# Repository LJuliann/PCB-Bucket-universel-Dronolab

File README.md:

# PCB Bucket universel — Dronolab

Conception électronique et routage KiCad du PCB Bucket universel de Dronolab.

## Projet principal

Ouvrir `Bucket_universel_v2.kicad_pro` dans KiCad.

Le dépôt contient le schéma principal, les feuilles hiérarchiques, le circuit imprimé,
les bibliothèques personnalisées et les fichiers de fabrication associés.

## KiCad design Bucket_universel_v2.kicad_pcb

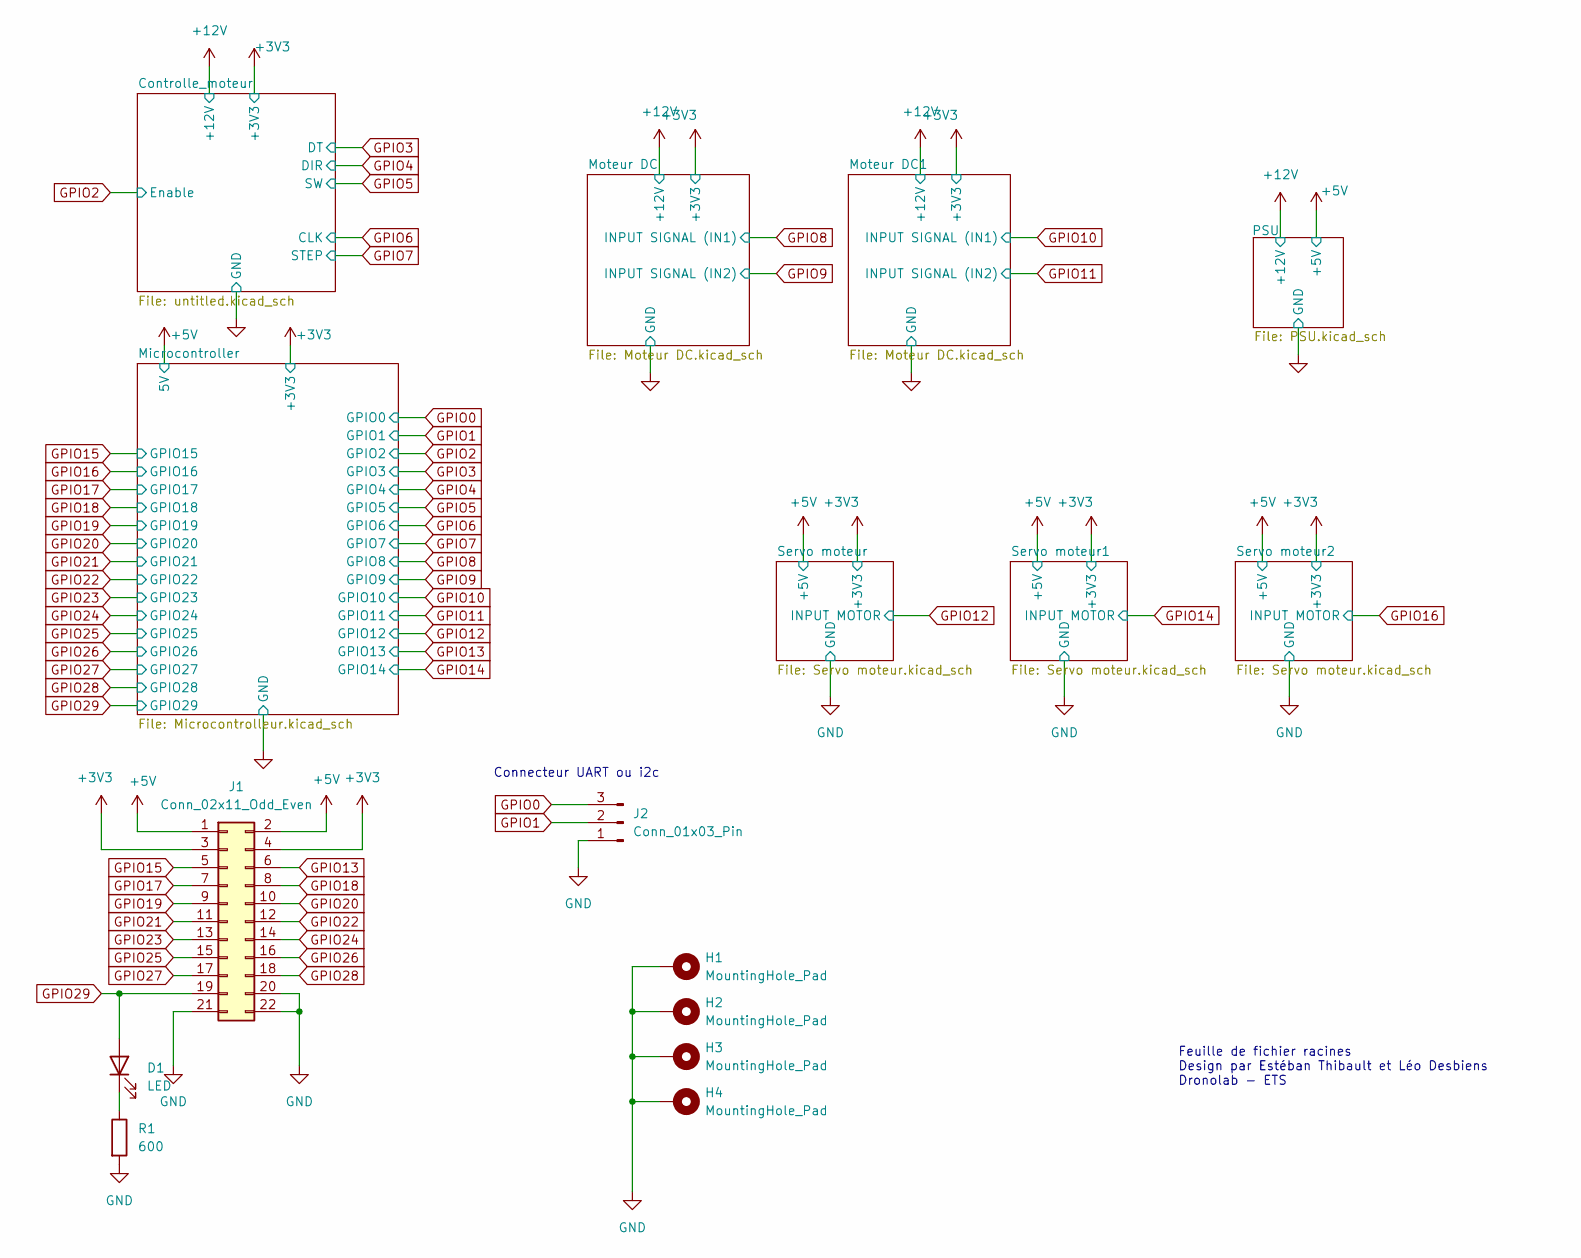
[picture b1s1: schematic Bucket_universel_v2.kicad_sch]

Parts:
D1: LED; LED_0603_1608Metric
H1, H2, H3, H4: MountingHole_Pad; MountingHole_3.2mm_M3_Pad
J1: Conn_02x11_Odd_Even; PinHeader_2x11_P2.00mm_Vertical
J2: Conn_01x03_Pin; JST_PH_S3B-PH-K_1x03_P2.00mm_Horizontal
R1: 600; R_0603_1608Metric

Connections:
+3V3: J1.3, J1.4; also elsewhere on the board
+5V: J1.1, J1.2; also elsewhere on the board
GND: H1.1 (1_1), H2.1 (1_1), H3.1 (1_1), H4.1 (1_1), J1.20, J1.21, J1.22, J2.1, R1.2; also elsewhere on the board
GPIO0: J2.3; also elsewhere on the board
GPIO1: J2.2; also elsewhere on the board
GPIO13: J1.6; also elsewhere on the board
GPIO15: J1.5; also elsewhere on the board
GPIO17: J1.7; also elsewhere on the board
GPIO18: J1.8; also elsewhere on the board
GPIO19: J1.9; also elsewhere on the board
GPIO20: J1.10; also elsewhere on the board
GPIO21: J1.11; also elsewhere on the board
GPIO22: J1.12; also elsewhere on the board
GPIO23: J1.13; also elsewhere on the board
GPIO24: J1.14; also elsewhere on the board
GPIO25: J1.15; also elsewhere on the board
GPIO26: J1.16; also elsewhere on the board
GPIO27: J1.17; also elsewhere on the board
GPIO28: J1.18; also elsewhere on the board
GPIO29: D1.2 (A), J1.19; also elsewhere on the board
unnamed: D1.1 (K), R1.1

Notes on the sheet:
Feuille de fichier racines Design par Estéban Thibault et Léo Desbiens Dronolab - ETS
Connecteur UART ou i2c

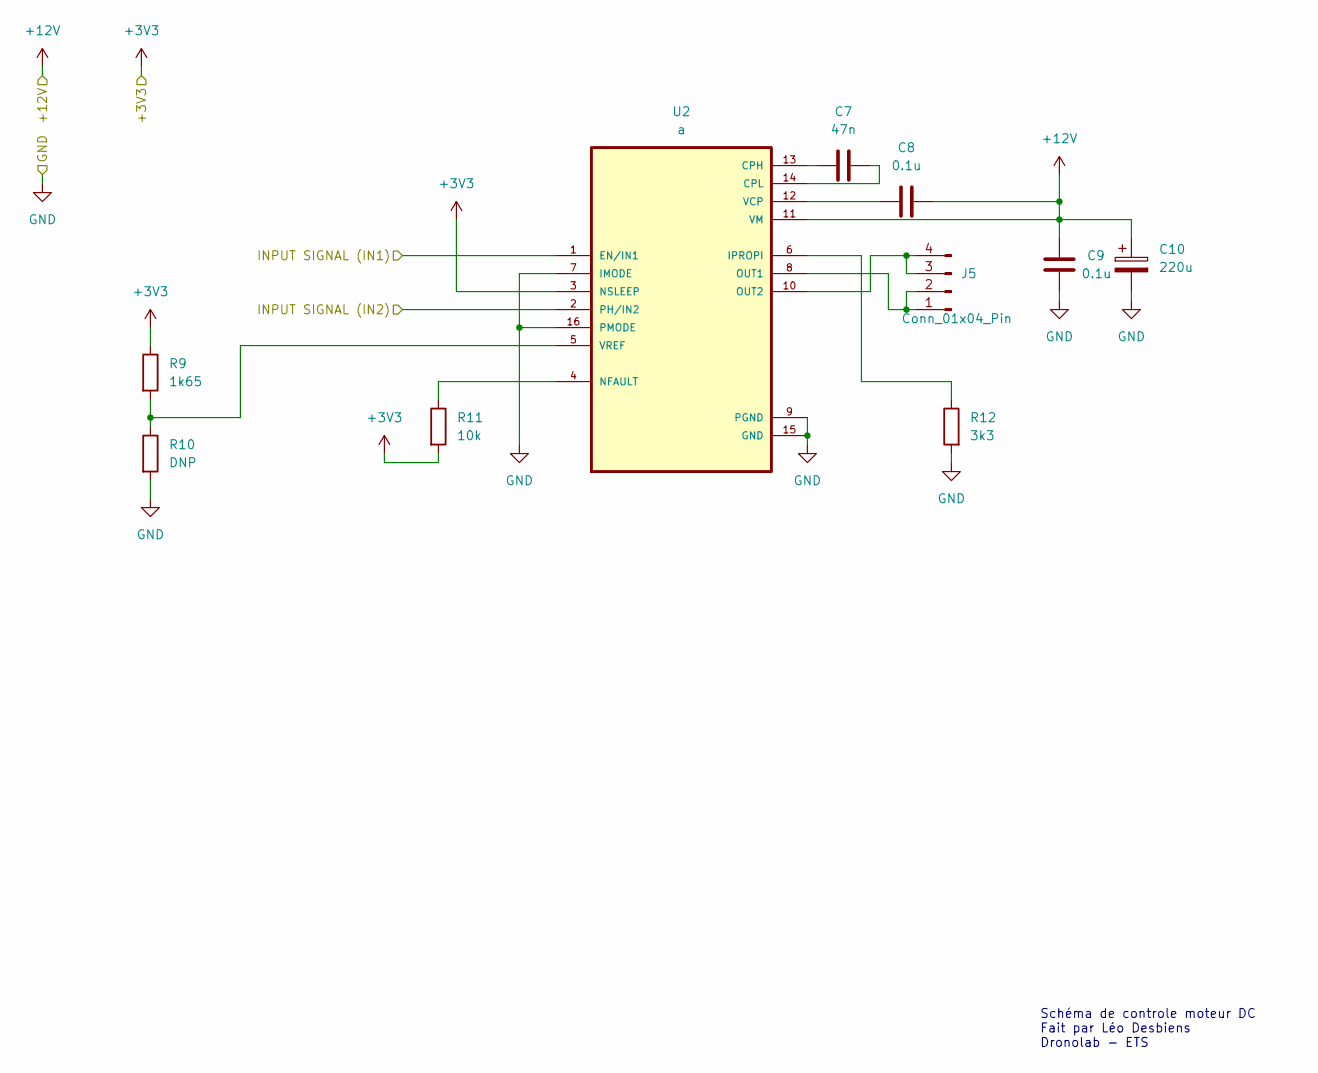
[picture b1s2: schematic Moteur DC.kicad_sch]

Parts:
C7: 47n; C_0603_1608Metric
C8, C9: 0.1u; C_0603_1608Metric
C10: 220u; CP_Elec_6.3x7.7
J5: Conn_01x04_Pin; JST_XH_S4B-XH-A_1x04_P2.50mm_Horizontal
R9: 1k65; R_0603_1608Metric
R10: DNP; R_0603_1608Metric
R11: 10k; R_0603_1608Metric
R12: 3k3; R_0603_1608Metric
U2: a; SOP65P640X120-17N

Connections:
+3V3: R9.1, R11.2, U2.3 (NSLEEP); also elsewhere on the board
+12V: C8.2, C9.2, C10.1, U2.11 (VM); also elsewhere on the board
GND: C9.1, C10.2, R10.2, R12.2, U2.7 (IMODE), U2.9 (PGND), U2.15 (GND), U2.16 (PMODE); also elsewhere on the board
GPIO8: U2.1 (EN/IN1); also elsewhere on the board
GPIO9: U2.2 (PH/IN2); also elsewhere on the board
unnamed: J5.1, J5.2, U2.8 (OUT1)
unnamed: J5.3, J5.4, U2.10 (OUT2)
unnamed: C7.1, U2.13 (CPH)
unnamed: C7.2, U2.14 (CPL)
unnamed: R12.1, U2.6 (IPROPI)
unnamed: R11.1, U2.4 (NFAULT)
unnamed: C8.1, U2.12 (VCP)
unnamed: R9.2, R10.1, U2.5 (VREF)

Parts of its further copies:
C35: 47n; C_0603_1608Metric
C36, C37: 0.1u; C_0603_1608Metric
C38: 220u; CP_Elec_6.3x7.7
J12: Conn_01x04_Pin; JST_XH_S4B-XH-A_1x04_P2.50mm_Horizontal
R28: 1k65; R_0603_1608Metric
R29: DNP; R_0603_1608Metric
R30: 10k; R_0603_1608Metric
R31: 3k3; R_0603_1608Metric
U11: a; SOP65P640X120-17N

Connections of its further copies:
+3V3: R28.1, R30.2, U11.3 (NSLEEP); also elsewhere on the board
+12V: C36.2, C37.2, C38.1, U11.11 (VM); also elsewhere on the board
GND: C37.1, C38.2, R29.2, R31.2, U11.7 (IMODE), U11.9 (PGND), U11.15 (GND), U11.16 (PMODE); also elsewhere on the board
GPIO10: U11.1 (EN/IN1); also elsewhere on the board
GPIO11: U11.2 (PH/IN2); also elsewhere on the board
unnamed: J12.1, J12.2, U11.8 (OUT1)
unnamed: J12.3, J12.4, U11.10 (OUT2)
unnamed: C35.1, U11.13 (CPH)
unnamed: C35.2, U11.14 (CPL)
unnamed: R31.1, U11.6 (IPROPI)
unnamed: R30.1, U11.4 (NFAULT)
unnamed: C36.1, U11.12 (VCP)
unnamed: R28.2, R29.1, U11.5 (VREF)

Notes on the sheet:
Schéma de controle moteur DC Fait par Léo Desbiens Dronolab - ETS

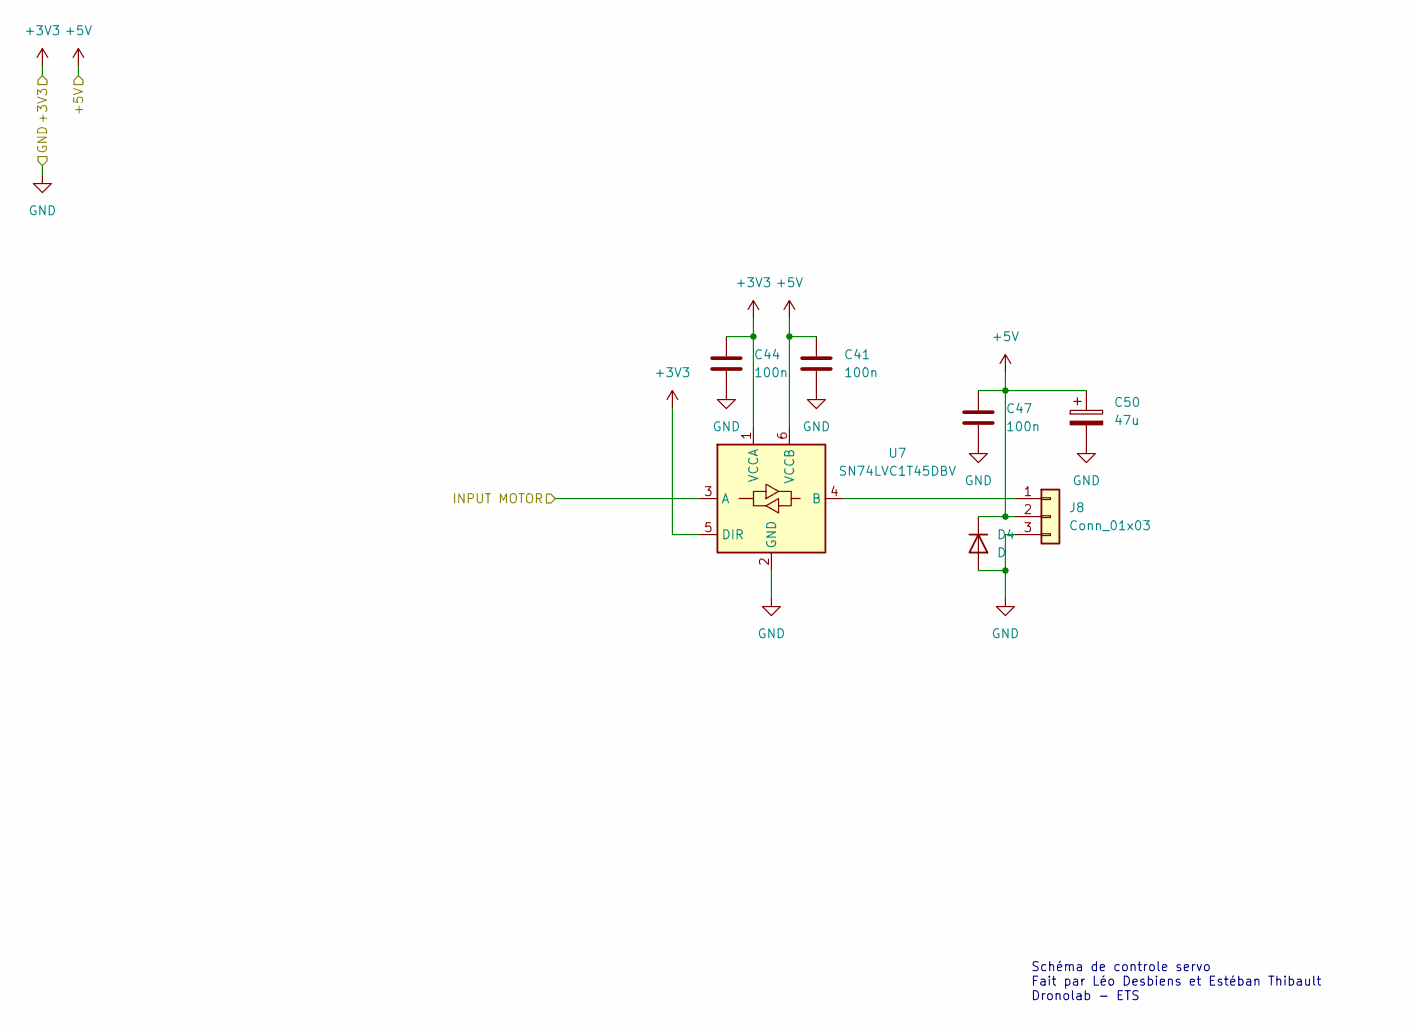
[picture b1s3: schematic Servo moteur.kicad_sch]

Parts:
C41, C44, C47: 100n; C_0603_1608Metric
C50: 47u; C_0603_1608Metric
D4: D; D_1206_3216Metric_Pad1.42x1.75mm_HandSolder
J8: Conn_01x03; JST_XH_S3B-XH-A_1x03_P2.50mm_Horizontal
U7: SN74LVC1T45DBV; SOT-23-6

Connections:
+3V3: C44.1, U7.1 (VCCA), U7.5 (DIR); also elsewhere on the board
+5V: C41.1, C47.1, C50.1, D4.1 (K), J8.2, U7.6 (VCCB); also elsewhere on the board
GND: C41.2, C44.2, C47.2, C50.2, D4.2 (A), J8.3, U7.2 (GND); also elsewhere on the board
GPIO12: U7.3 (A); also elsewhere on the board
unnamed: J8.1, U7.4 (B)

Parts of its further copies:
C42, C43, C45, C46, C48, C49: 100n; C_0603_1608Metric
C51, C52: 47u; C_0603_1608Metric
D6, D7: D; D_1206_3216Metric_Pad1.42x1.75mm_HandSolder
J10, J11: Conn_01x03; JST_XH_S3B-XH-A_1x03_P2.50mm_Horizontal
U9, U10: SN74LVC1T45DBV; SOT-23-6

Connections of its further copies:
+3V3: C45.1, C46.1, U9.1 (VCCA), U9.5 (DIR), U10.1 (VCCA), U10.5 (DIR); also elsewhere on the board
+5V: C42.1, C43.1, C48.1, C49.1, C51.1, C52.1, D6.1 (K), D7.1 (K), J10.2, J11.2, U9.6 (VCCB), U10.6 (VCCB); also elsewhere on the board
GND: C42.2, C43.2, C45.2, C46.2, C48.2, C49.2, C51.2, C52.2, D6.2 (A), D7.2 (A), J10.3, J11.3, U9.2 (GND), U10.2 (GND); also elsewhere on the board
GPIO14: U9.3 (A); also elsewhere on the board
GPIO16: U10.3 (A); also elsewhere on the board
unnamed: J10.1, U9.4 (B)
unnamed: J11.1, U10.4 (B)

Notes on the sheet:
Schéma de controle servo Fait par Léo Desbiens et Estéban Thibault Dronolab - ETS

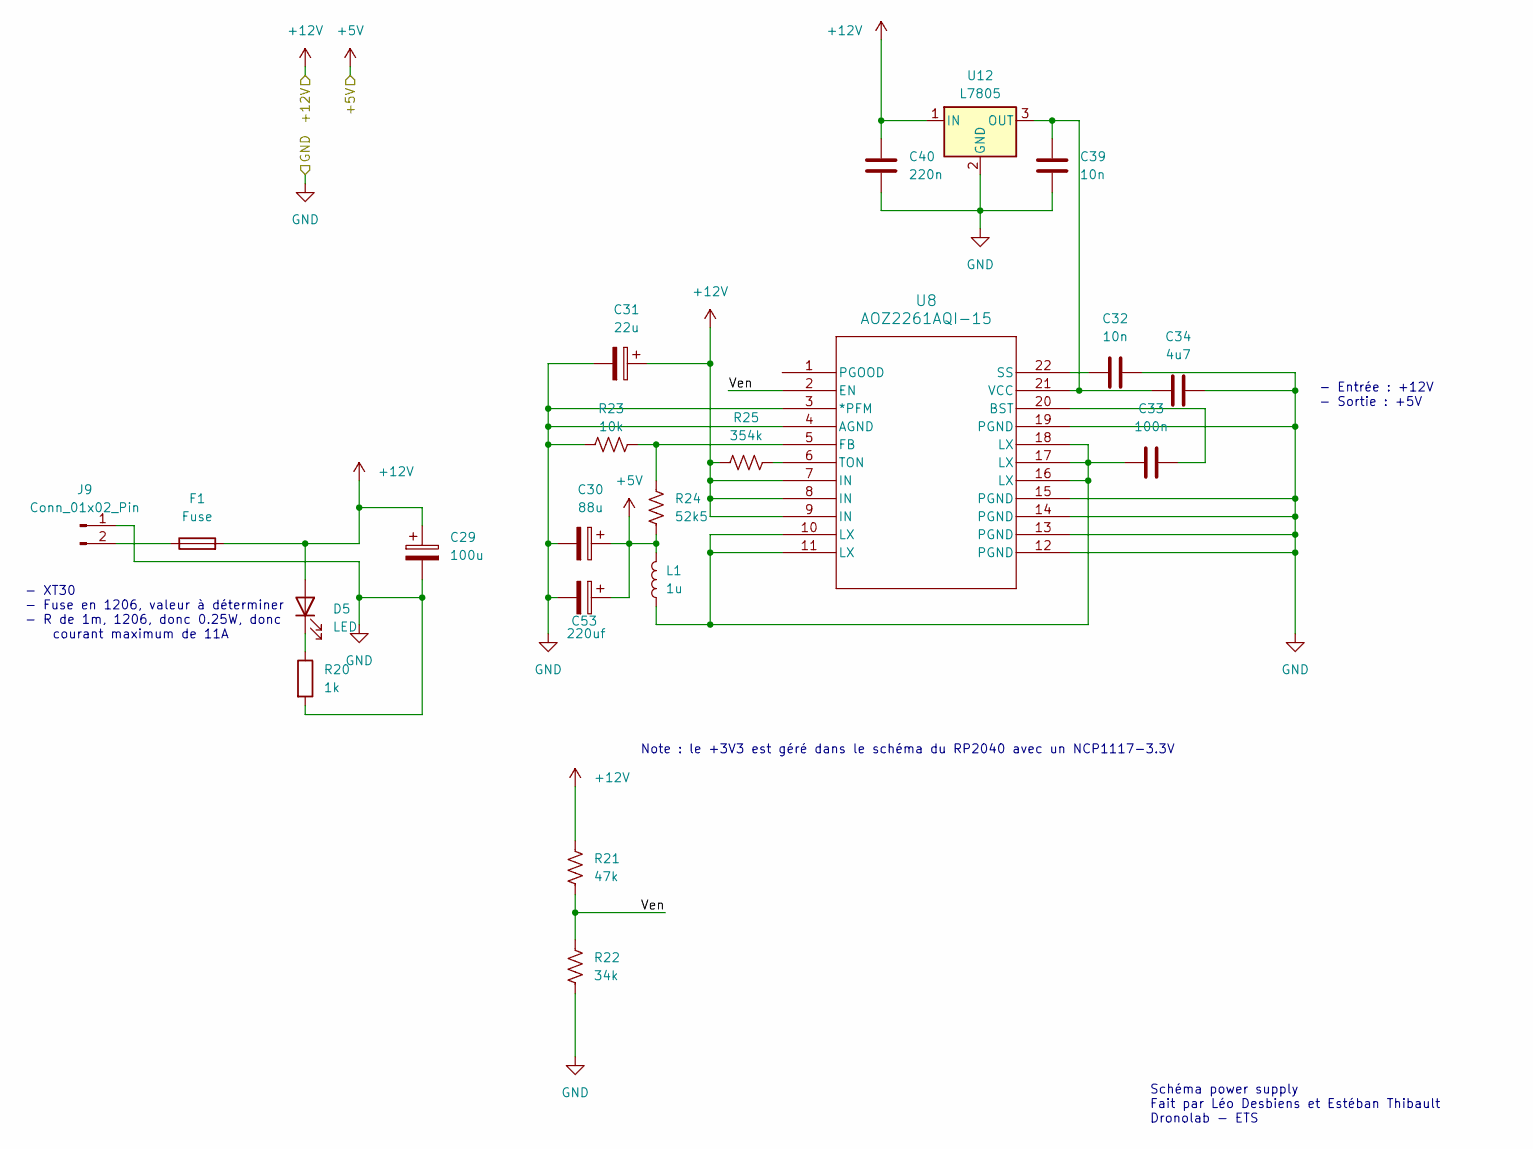
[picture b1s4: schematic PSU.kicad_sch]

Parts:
C29: 100u; CP_Elec_6.3x7.7
C30: 88u; CP_Elec_6.3x7.7
C31: 22u; CP_Elec_5x5.7
C32, C39: 10n; C_0603_1608Metric
C33: 100n; C_0603_1608Metric
C34: 4u7; C_0603_1608Metric
C40: 220n; C_0603_1608Metric
C53: 220uf; CP_Elec_6.3x7.7
D5: LED; LED_0603_1608Metric
F1: Fuse; Fuse_1206_3216Metric
J9: Conn_01x02_Pin; AMASS_XT30PW-M_1x02_P2.50mm_Horizontal
L1: 1u; L_Vishay_IHLP-2525
R20: 1k; R_0603_1608Metric
R21: 47k; R_0603_1608Metric
R22: 34k; R_0603_1608Metric
R23: 10k; R_0603_1608Metric
R24: 52k5; R_0603_1608Metric
R25: 354k; R_0603_1608Metric
U8: AOZ2261AQI-15; IC_MP2722GRH-0000-Z
U12: L7805; DCY4_TEX

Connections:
+5V: C30.1, C53.1, L1.2, R24.2; also elsewhere on the board
+12V: C29.1, C31.1, C40.2, D5.2 (A), F1.2, R21.1, R25.1, U8.7 (IN), U8.8 (IN), U8.9 (IN), U12.1 (IN); also elsewhere on the board
/PSU/Ven: R21.2, R22.1, U8.2 (EN)
GND: C29.2, C30.2, C31.2, C32.2, C34.2, C39.2, C40.1, C53.2, J9.1, R20.2, R22.2, R23.2, U8.3 (*PFM), U8.4 (AGND), U8.12 (PGND), U8.13 (PGND), U8.14 (PGND), U8.15 (PGND), U8.19 (PGND), U12.2 (GND); also elsewhere on the board
unnamed: C33.2, L1.1, U8.10 (LX), U8.11 (LX), U8.16 (LX), U8.17 (LX), U8.18 (LX)
unnamed: D5.1 (K), R20.1
unnamed: F1.1, J9.2
unnamed: C33.1, U8.20 (BST)
unnamed: R23.1, R24.1, U8.5 (FB)
unnamed: C32.1, U8.22 (SS)
unnamed: R25.2, U8.6 (TON)
unnamed: C34.1, C39.1, U8.21 (VCC), U12.3 (OUT)

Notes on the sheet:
Note : le +3V3 est géré dans le schéma du RP2040 avec un NCP1117-3.3V
- Entrée : +12V - Sortie : +5V
- XT30 - Fuse en 1206, valeur à déterminer - R de 1m, 1206, donc 0.25W, donc courant maximum de 11A
Schéma power supply Fait par Léo Desbiens et Estéban Thibault Dronolab - ETS

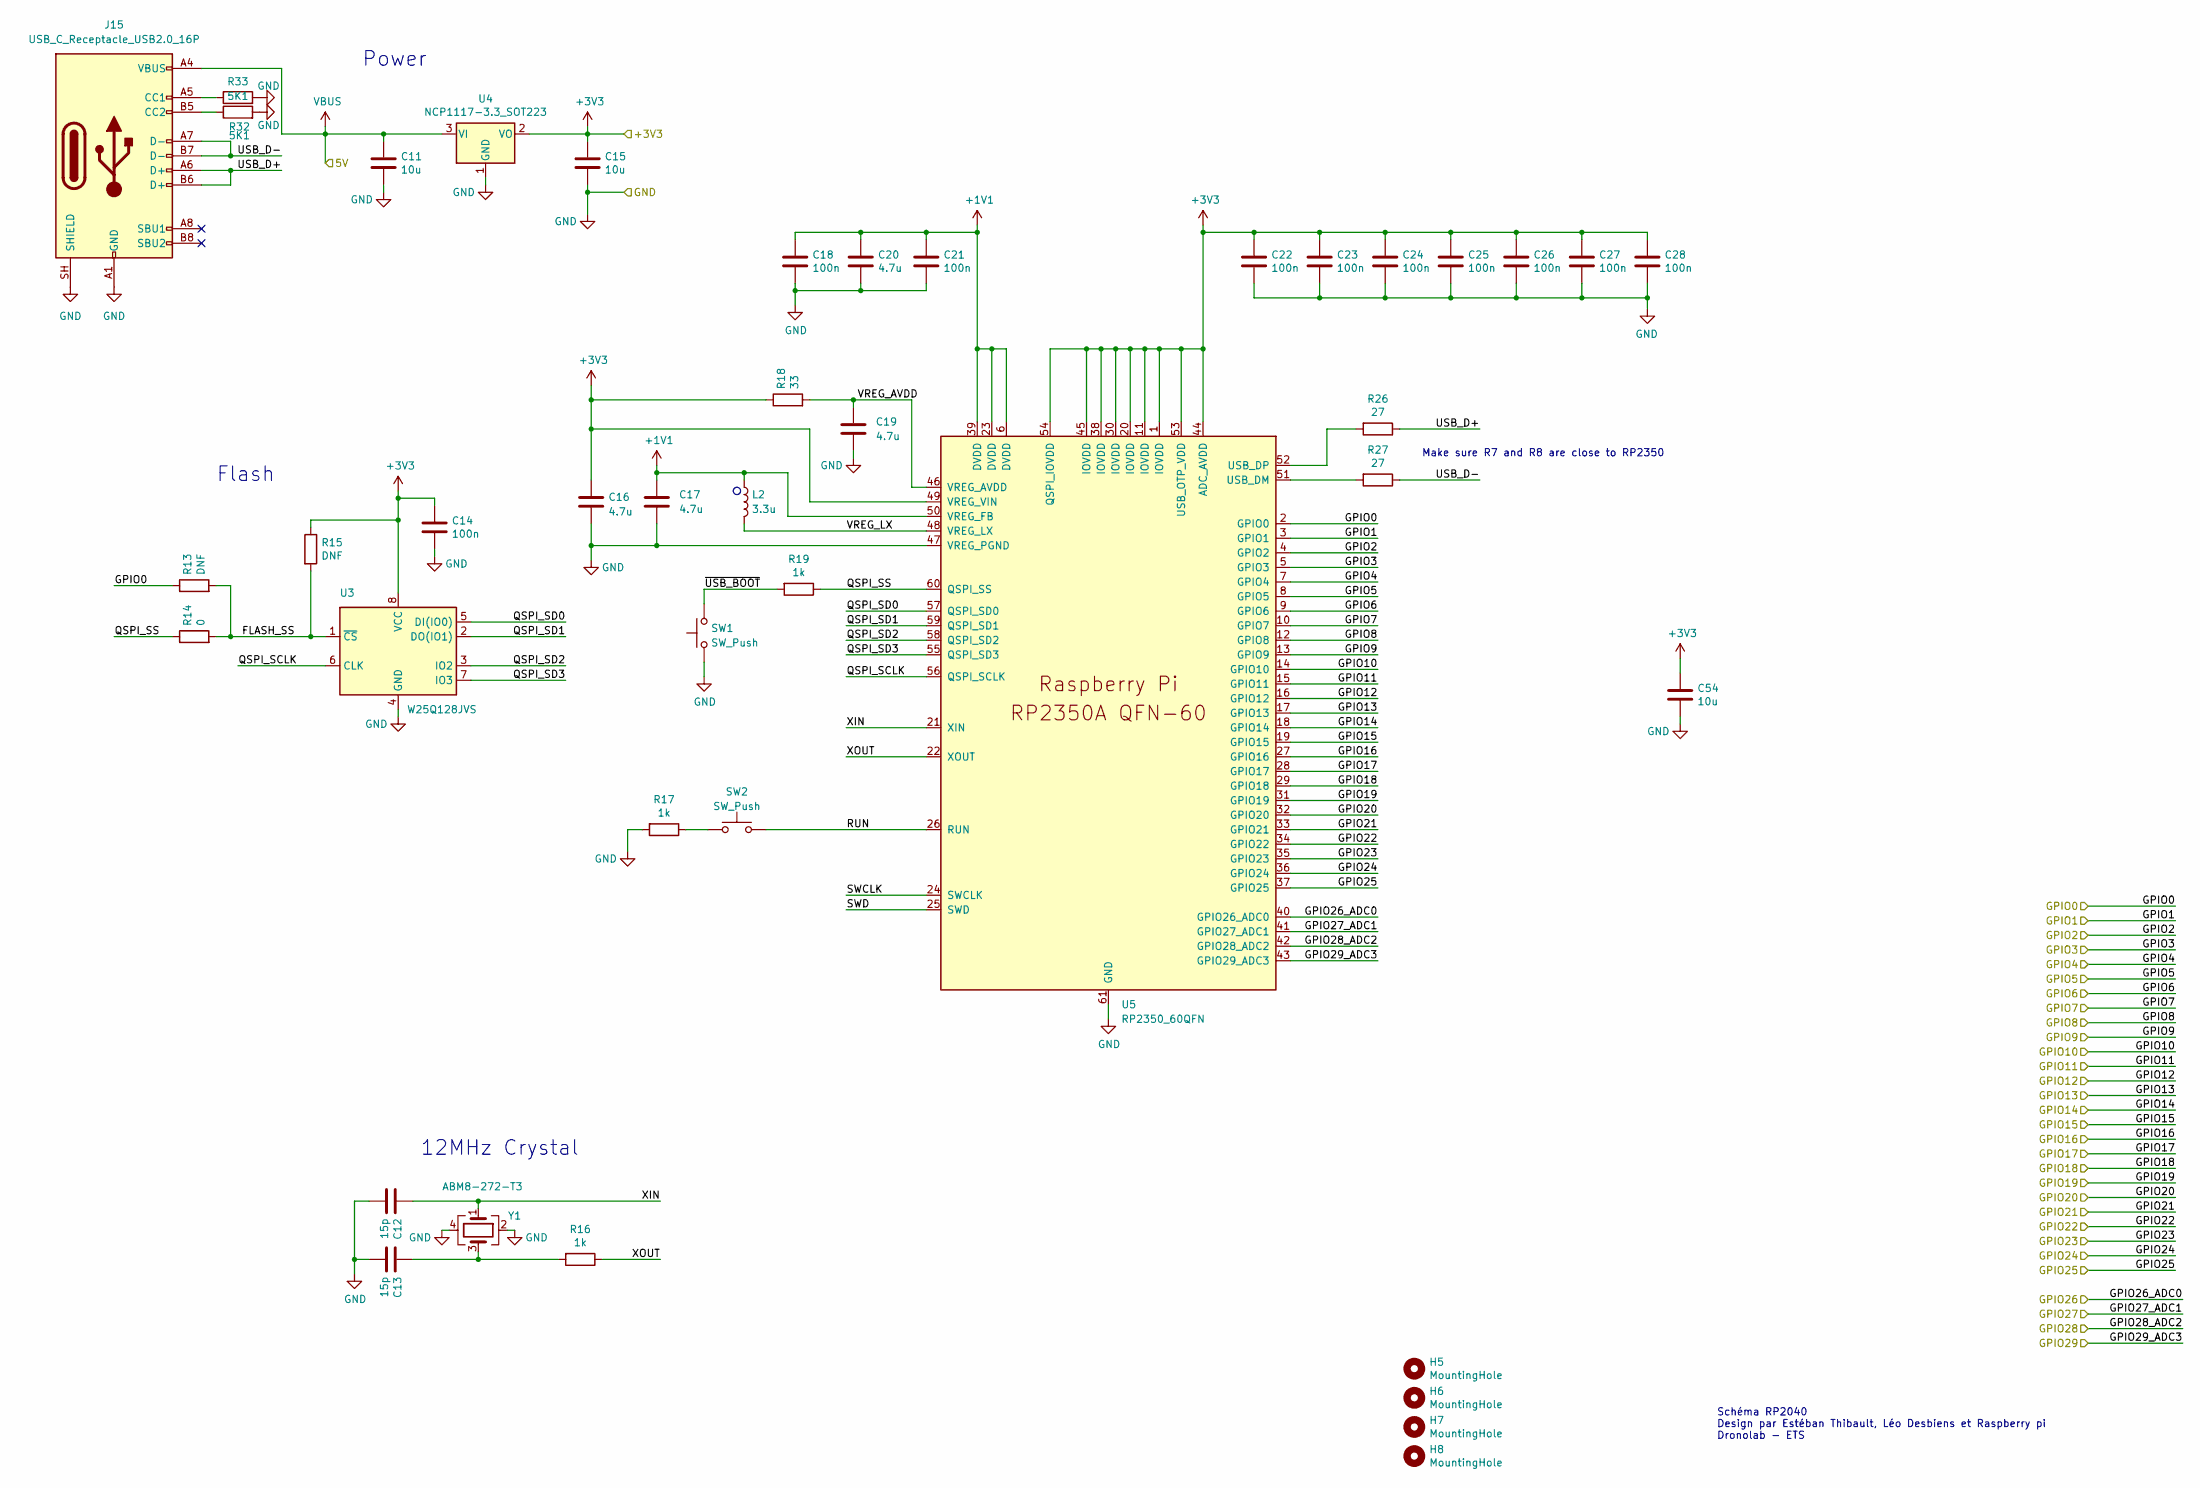
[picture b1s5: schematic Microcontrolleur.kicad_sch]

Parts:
C11, C15, C54: 10u; C_0805_2012Metric
C12, C13: 15p; C_0402_1005Metric
C14, C18, C21, C22, C23, C24, C25, C26, C27, C28: 100n; C_0402_1005Metric
C16, C17: 4.7u; C_0402_1005Metric_small_pads
C19, C20: 4.7u; C_0402_1005Metric
H5, H6, H7, H8: MountingHole; MountingHole_2.7mm_M2.5
J15: USB_C_Receptacle_USB2.0_16P; USB_C_Receptacle_GCT_USB4105-xx-A_16P_TopMnt_Horizontal
L2: 3.3u; L_pol_2016
R13, R15: DNF; R_0402_1005Metric
R14: 0; R_0402_1005Metric
R16, R17, R19: 1k; R_0402_1005Metric
R18: 33; R_0402_1005Metric
R26, R27: 27; R_0402_1005Metric
R32, R33: 5K1; R_0402_1005Metric
SW1, SW2: SW_Push; SW_Push_1P1T_NO_Vertical_Wuerth_434133025816
U3: W25Q128JVS; SOIC-8_5.3x5.3mm_P1.27mm
U4: NCP1117-3.3_SOT223; SOT-223-3_TabPin2
U5: RP2350_60QFN; RP2350-QFN-60-1EP_7x7_P0.4mm_EP3.4x3.4mm_ThermalVias
Y1: ABM8-272-T3; Crystal_SMD_3225-4Pin_3.2x2.5mm

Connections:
+1V1: C17.1, C18.1, C20.1, C21.1, L2.1, U5.6 (DVDD), U5.23 (DVDD), U5.39 (DVDD), U5.50 (VREG_FB)
+3V3: C14.1, C15.1, C16.1, C22.1, C23.1, C24.1, C25.1, C26.1, C27.1, C28.1, C54.1, R15.1, R18.1, U3.8 (VCC), U4.2 (VO), U5.1 (IOVDD), U5.11 (IOVDD), U5.20 (IOVDD), U5.30 (IOVDD), U5.38 (IOVDD), U5.44 (ADC_AVDD), U5.45 (IOVDD), U5.49 (VREG_VIN), U5.53 (USB_OTP_VDD), U5.54 (QSPI_IOVDD); also elsewhere on the board
+5V: C11.1, J15.A4 (VBUS), J15.A9 (VBUS), J15.B4 (VBUS), J15.B9 (VBUS), U4.3 (VI); also elsewhere on the board
/Microcontroller/FLASH_SS: R13.2, R14.2, R15.2, U3.1 (~CS)
/Microcontroller/QSPI_SCLK: U3.6 (CLK), U5.56 (QSPI_SCLK)
/Microcontroller/QSPI_SD0: U3.5 (DI(IO0)), U5.57 (QSPI_SD0)
/Microcontroller/QSPI_SD1: U3.2 (DO(IO1)), U5.59 (QSPI_SD1)
/Microcontroller/QSPI_SD2: U3.3 (IO2), U5.58 (QSPI_SD2)
/Microcontroller/QSPI_SD3: U3.7 (IO3), U5.55 (QSPI_SD3)
/Microcontroller/QSPI_SS: R14.1, R19.1, U5.60 (QSPI_SS)
/Microcontroller/RUN: SW2.2, U5.26 (RUN)
/Microcontroller/SWCLK: U5.24 (SWCLK)
/Microcontroller/SWD: U5.25 (SWD)
/Microcontroller/USB_D+: J15.A6 (D+), J15.B6 (D+), R26.1
/Microcontroller/USB_D-: J15.A7 (D-), J15.B7 (D-), R27.1
/Microcontroller/VREG_AVDD: C19.1, R18.2, U5.46 (VREG_AVDD)
/Microcontroller/VREG_LX: L2.2, U5.48 (VREG_LX)
/Microcontroller/XIN: C12.1, U5.21 (XIN), Y1.1
/Microcontroller/XOUT: R16.1, U5.22 (XOUT)
/Microcontroller/~USB_BOOT: R19.2, SW1.2
GND: C11.2, C12.2, C13.2, C14.2, C15.2, C16.2, C17.2, C18.2, C19.2, C20.2, C21.2, C22.2, C23.2, C24.2, C25.2, C26.2, C27.2, C28.2, C54.2, J15.A1 (GND), J15.A12 (GND), J15.B1 (GND), J15.B12 (GND), J15.SH (SHIELD), R17.2, R32.2, R33.2, SW1.1, U3.4 (GND), U4.1 (GND), U5.47 (VREG_PGND), U5.61 (GND), Y1.2, Y1.4; also elsewhere on the board
GPIO0: R13.1, U5.2 (GPIO0); also elsewhere on the board
GPIO1: U5.3 (GPIO1); also elsewhere on the board
GPIO2: U5.4 (GPIO2); also elsewhere on the board
GPIO3: U5.5 (GPIO3); also elsewhere on the board
GPIO4: U5.7 (GPIO4); also elsewhere on the board
GPIO5: U5.8 (GPIO5); also elsewhere on the board
GPIO6: U5.9 (GPIO6); also elsewhere on the board
GPIO7: U5.10 (GPIO7); also elsewhere on the board
GPIO8: U5.12 (GPIO8); also elsewhere on the board
GPIO9: U5.13 (GPIO9); also elsewhere on the board
GPIO10: U5.14 (GPIO10); also elsewhere on the board
GPIO11: U5.15 (GPIO11); also elsewhere on the board
GPIO12: U5.16 (GPIO12); also elsewhere on the board
GPIO13: U5.17 (GPIO13); also elsewhere on the board
GPIO14: U5.18 (GPIO14); also elsewhere on the board
GPIO15: U5.19 (GPIO15); also elsewhere on the board
GPIO16: U5.27 (GPIO16); also elsewhere on the board
GPIO17: U5.28 (GPIO17); also elsewhere on the board
GPIO18: U5.29 (GPIO18); also elsewhere on the board
GPIO19: U5.31 (GPIO19); also elsewhere on the board
GPIO20: U5.32 (GPIO20); also elsewhere on the board
GPIO21: U5.33 (GPIO21); also elsewhere on the board
GPIO22: U5.34 (GPIO22); also elsewhere on the board
GPIO23: U5.35 (GPIO23); also elsewhere on the board
GPIO24: U5.36 (GPIO24); also elsewhere on the board
GPIO25: U5.37 (GPIO25); also elsewhere on the board
GPIO26: U5.40 (GPIO26_ADC0); also elsewhere on the board
GPIO27: U5.41 (GPIO27_ADC1); also elsewhere on the board
GPIO28: U5.42 (GPIO28_ADC2); also elsewhere on the board
GPIO29: U5.43 (GPIO29_ADC3); also elsewhere on the board
unnamed: C13.1, R16.2, Y1.3
unnamed: J15.A5 (CC1), R33.1
unnamed: J15.B5 (CC2), R32.1
unnamed: R17.1, SW2.1
unnamed: R27.2, U5.51 (USB_DM)
unnamed: R26.2, U5.52 (USB_DP)

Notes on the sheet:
Power
Flash
12MHz Crystal
Make sure R7 and R8 are close to RP2350
Schéma RP2040 Design par Estéban Thibault, Léo Desbiens et Raspberry pi Dronolab - ETS

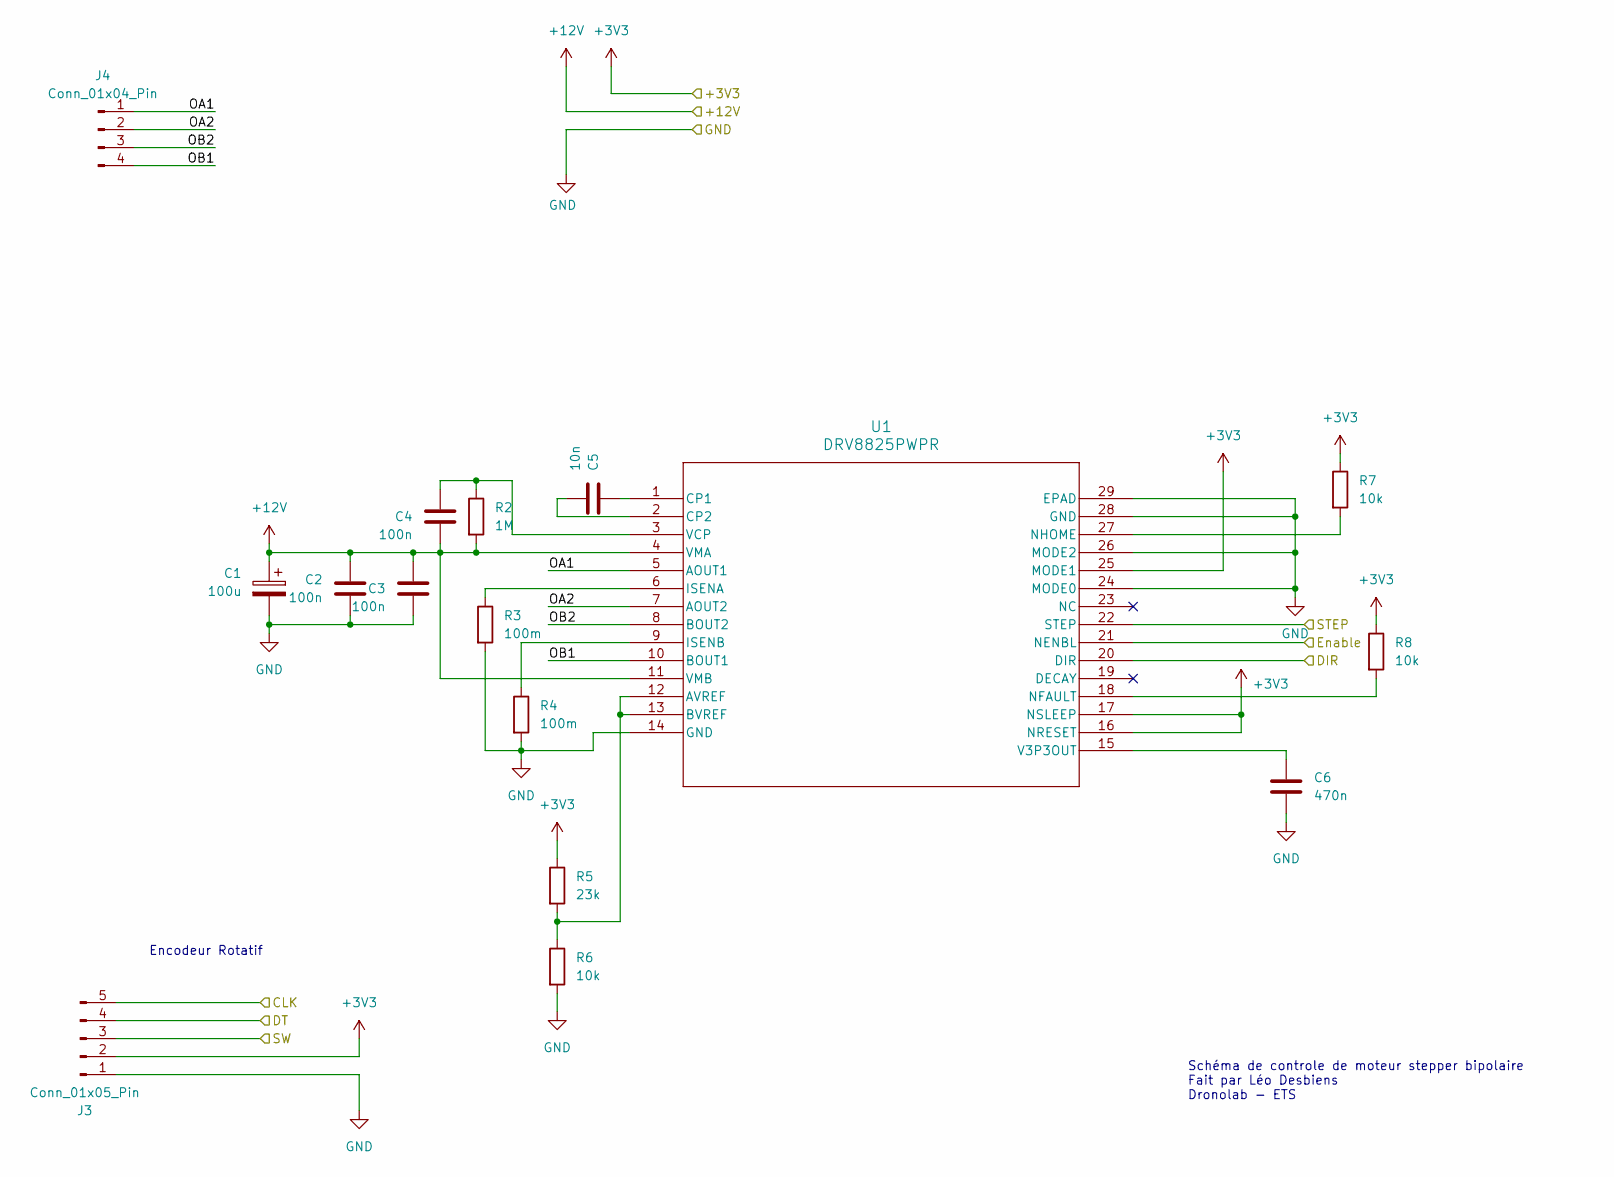
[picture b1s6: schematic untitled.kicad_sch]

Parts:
C1: 100u; CP_Elec_6.3x7.7
C2, C3, C4: 100n; C_0603_1608Metric
C5: 10n; C_0603_1608Metric
C6: 470n; C_0603_1608Metric
J3: Conn_01x05_Pin; JST_PH_S5B-PH-K_1x05_P2.00mm_Horizontal
J4: Conn_01x04_Pin; JST_XH_S4B-XH-A_1x04_P2.50mm_Horizontal
R2: 1M; R_0603_1608Metric
R3, R4: 100m; R_0603_1608Metric
R5: 23k; R_0603_1608Metric
R6, R7, R8: 10k; R_0603_1608Metric
U1: DRV8825PWPR; PWP28_5P18X3P1

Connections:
+3V3: J3.2, R5.1, R7.1, R8.1, U1.16 (NRESET), U1.17 (NSLEEP), U1.25 (MODE1); also elsewhere on the board
+12V: C1.1, C2.1, C3.1, C4.2, R2.2, U1.4 (VMA), U1.11 (VMB); also elsewhere on the board
/Controlle_moteur/OA1: J4.1, U1.5 (AOUT1)
/Controlle_moteur/OA2: J4.2, U1.7 (AOUT2)
/Controlle_moteur/OB1: J4.4, U1.10 (BOUT1)
/Controlle_moteur/OB2: J4.3, U1.8 (BOUT2)
GND: C1.2, C2.2, C3.2, C6.2, J3.1, R3.2, R4.2, R6.2, U1.14 (GND), U1.24 (MODE0), U1.26 (MODE2), U1.28 (GND), U1.29 (EPAD); also elsewhere on the board
GPIO2: U1.21 (NENBL); also elsewhere on the board
GPIO3: J3.4; also elsewhere on the board
GPIO4: U1.20 (DIR); also elsewhere on the board
GPIO5: J3.3; also elsewhere on the board
GPIO6: J3.5; also elsewhere on the board
GPIO7: U1.22 (STEP); also elsewhere on the board
unnamed: R5.2, R6.1, U1.12 (AVREF), U1.13 (BVREF)
unnamed: C5.1, U1.1 (CP1)
unnamed: C5.2, U1.2 (CP2)
unnamed: R3.1, U1.6 (ISENA)
unnamed: R4.1, U1.9 (ISENB)
unnamed: R8.2, U1.18 (NFAULT)
unnamed: R7.2, U1.27 (NHOME)
unnamed: C6.1, U1.15 (V3P3OUT)
unnamed: C4.1, R2.1, U1.3 (VCP)

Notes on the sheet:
Schéma de controle de moteur stepper bipolaire Fait par Léo Desbiens Dronolab - ETS
Encodeur Rotatif

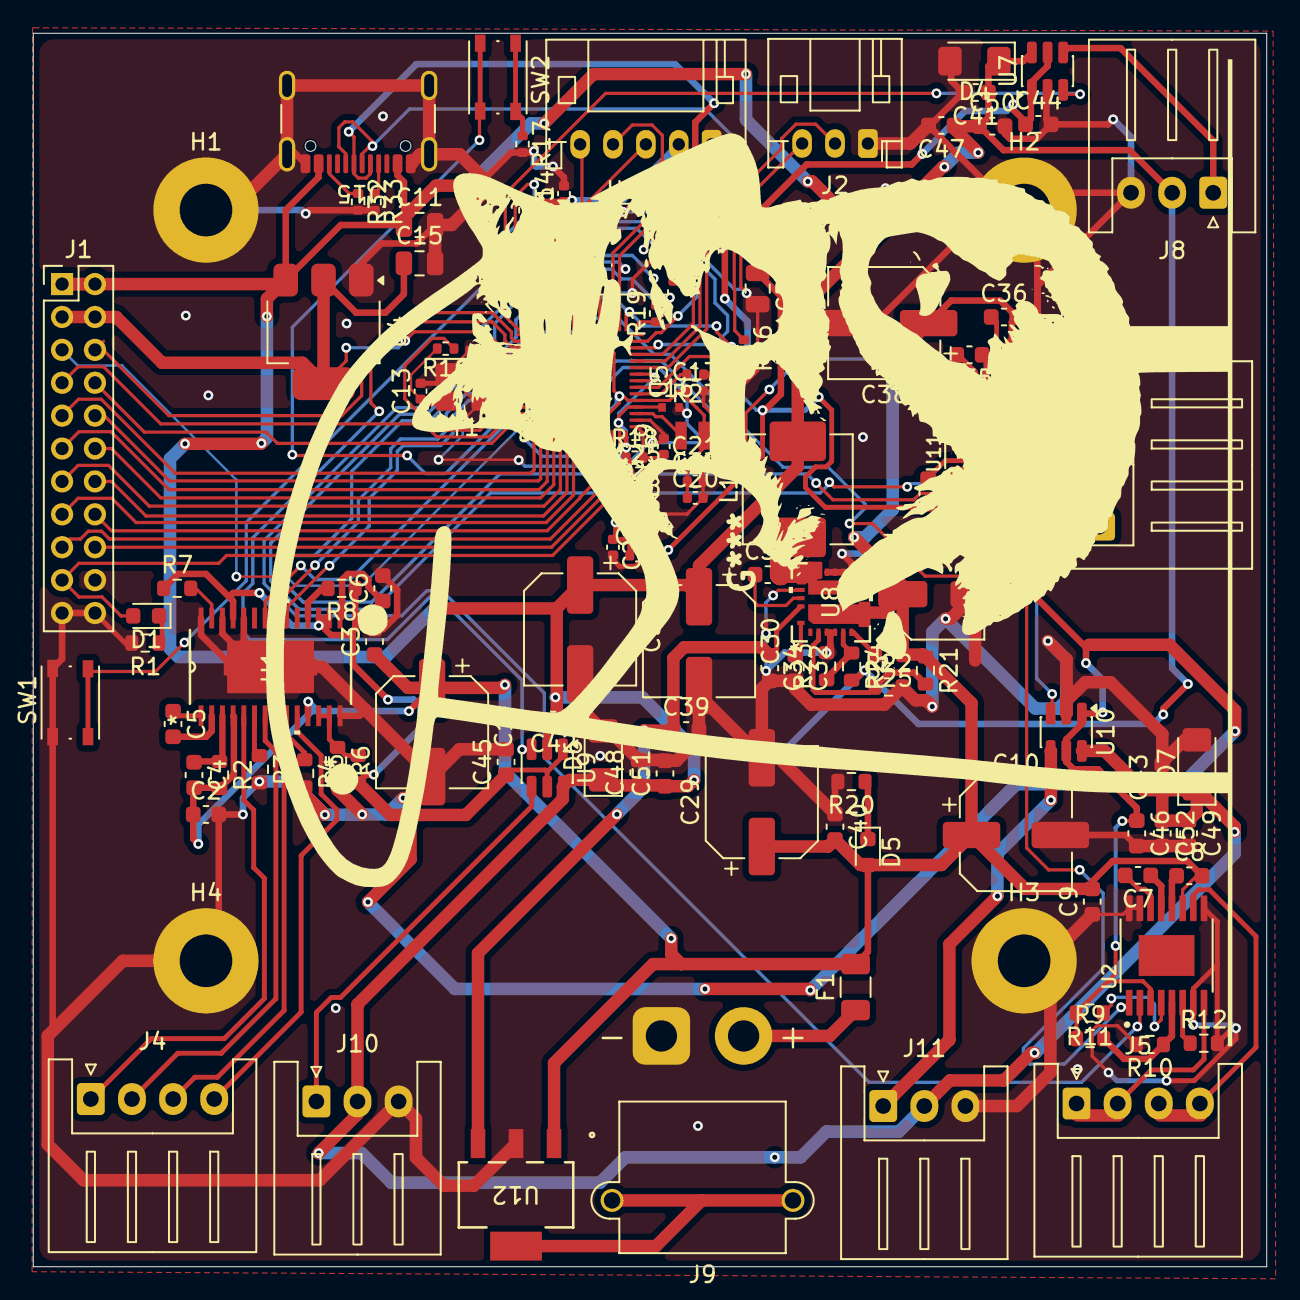
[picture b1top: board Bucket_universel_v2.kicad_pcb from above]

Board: 2 copper layers, 75.0 x 75.0 mm, 124 parts (0 on the bottom side), 98 nets.
